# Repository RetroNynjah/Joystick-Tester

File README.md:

# Retro Ninja Joystick-Tester
 Tester for 9-pin Atari and Commodore compatible joysticks.

## BOM
 |Component|Pcs |Names|Comment|
 |:--------|---:|:---|:------|
 | CR2032 coin cell holder | 1 | BT1 | 30mm SMD or 20mm throuh-hole. Digikey BU2032SM-BT-GTR, BS-7-ND or similar|
 | 1206 SMD red LED | 1 | D5 | |
 | 1206 SMD green LED | 4 | D1, D2, D3, D4 | |
 | 0805 SMD resistor 220Ω | 5 | R1, R2, R3, R4, R5 ||
 | DE-9M 9-pin male D-sub connector | 1 | X1 |straight connectors or solder cups |

Retro Ninja

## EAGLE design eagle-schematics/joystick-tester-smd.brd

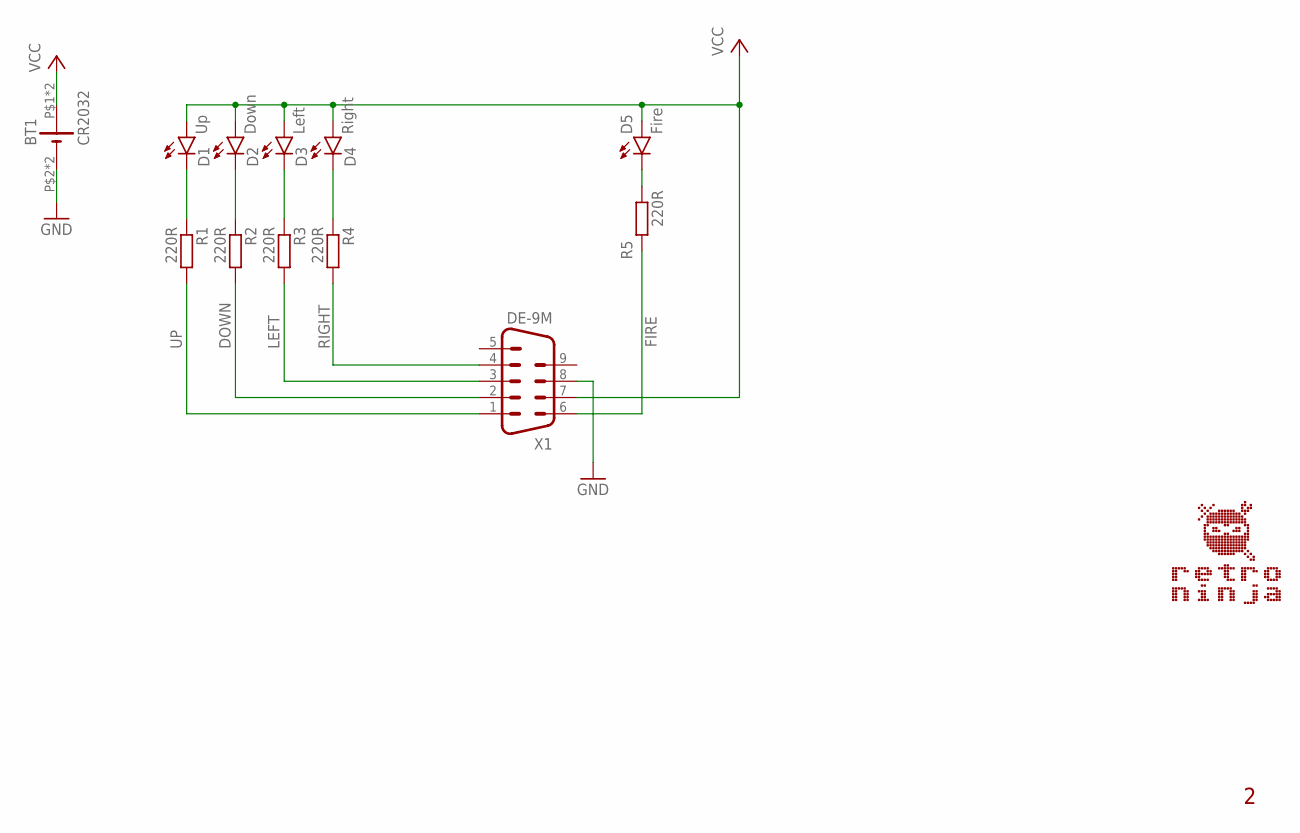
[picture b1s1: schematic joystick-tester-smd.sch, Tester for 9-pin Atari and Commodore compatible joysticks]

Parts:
BT1: CR2032; CR2032_2P30SMD_20MM_COMBO
D1: Up; LED-1206
D2: Down; LED-1206
D3: Left; LED-1206
D4: Right; LED-1206
D5: Fire; LED-1206
R1, R2, R3, R4, R5: 220R; M0805
X1: DE-9M; M09D

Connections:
DOWN: R2.2, X1.2
FIRE: R5.1, X1.6
GND: BT1.P$2 (-), BT1.P$4 (-), X1.8
LEFT: R3.2, X1.3
unnamed: D4.C, R4.1
unnamed: D5.C, R5.2
unnamed: D1.C, R1.1
unnamed: D2.C, R2.1
unnamed: D3.C, R3.1
RIGHT: R4.2, X1.4
UP: R1.2, X1.1
VCC: BT1.P$1 (+), BT1.P$3 (+), D1.A, D2.A, D3.A, D4.A, D5.A, X1.7

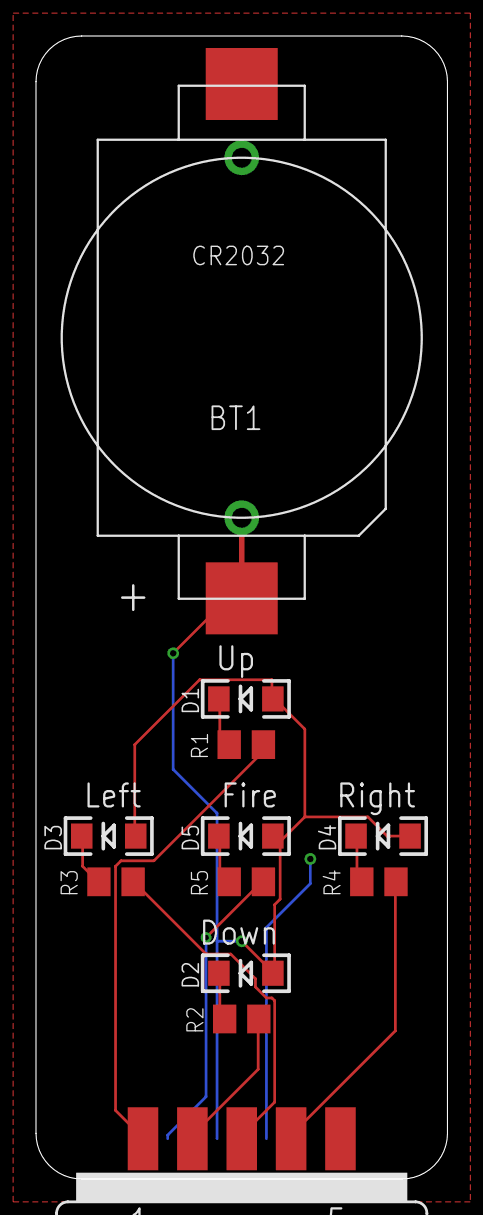
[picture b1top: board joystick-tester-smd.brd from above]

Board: 2 copper layers, 22.9 x 63.5 mm, 13 parts (1 on the bottom side), 12 nets.

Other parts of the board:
U$2: OSHW_8MM

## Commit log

2019-12-19 First version
2019-12-19 Updated battery layout
2019-12-19 Update README.md
    BOM updated
2019-12-19 Update schematics
2019-12-19 Update gerbers

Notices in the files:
parts and their libraries:
SparkFun-LED: Licensing: Creative Commons ShareAlike 4.0 International - https://creativecommons.org/licenses/by-sa/4.0
